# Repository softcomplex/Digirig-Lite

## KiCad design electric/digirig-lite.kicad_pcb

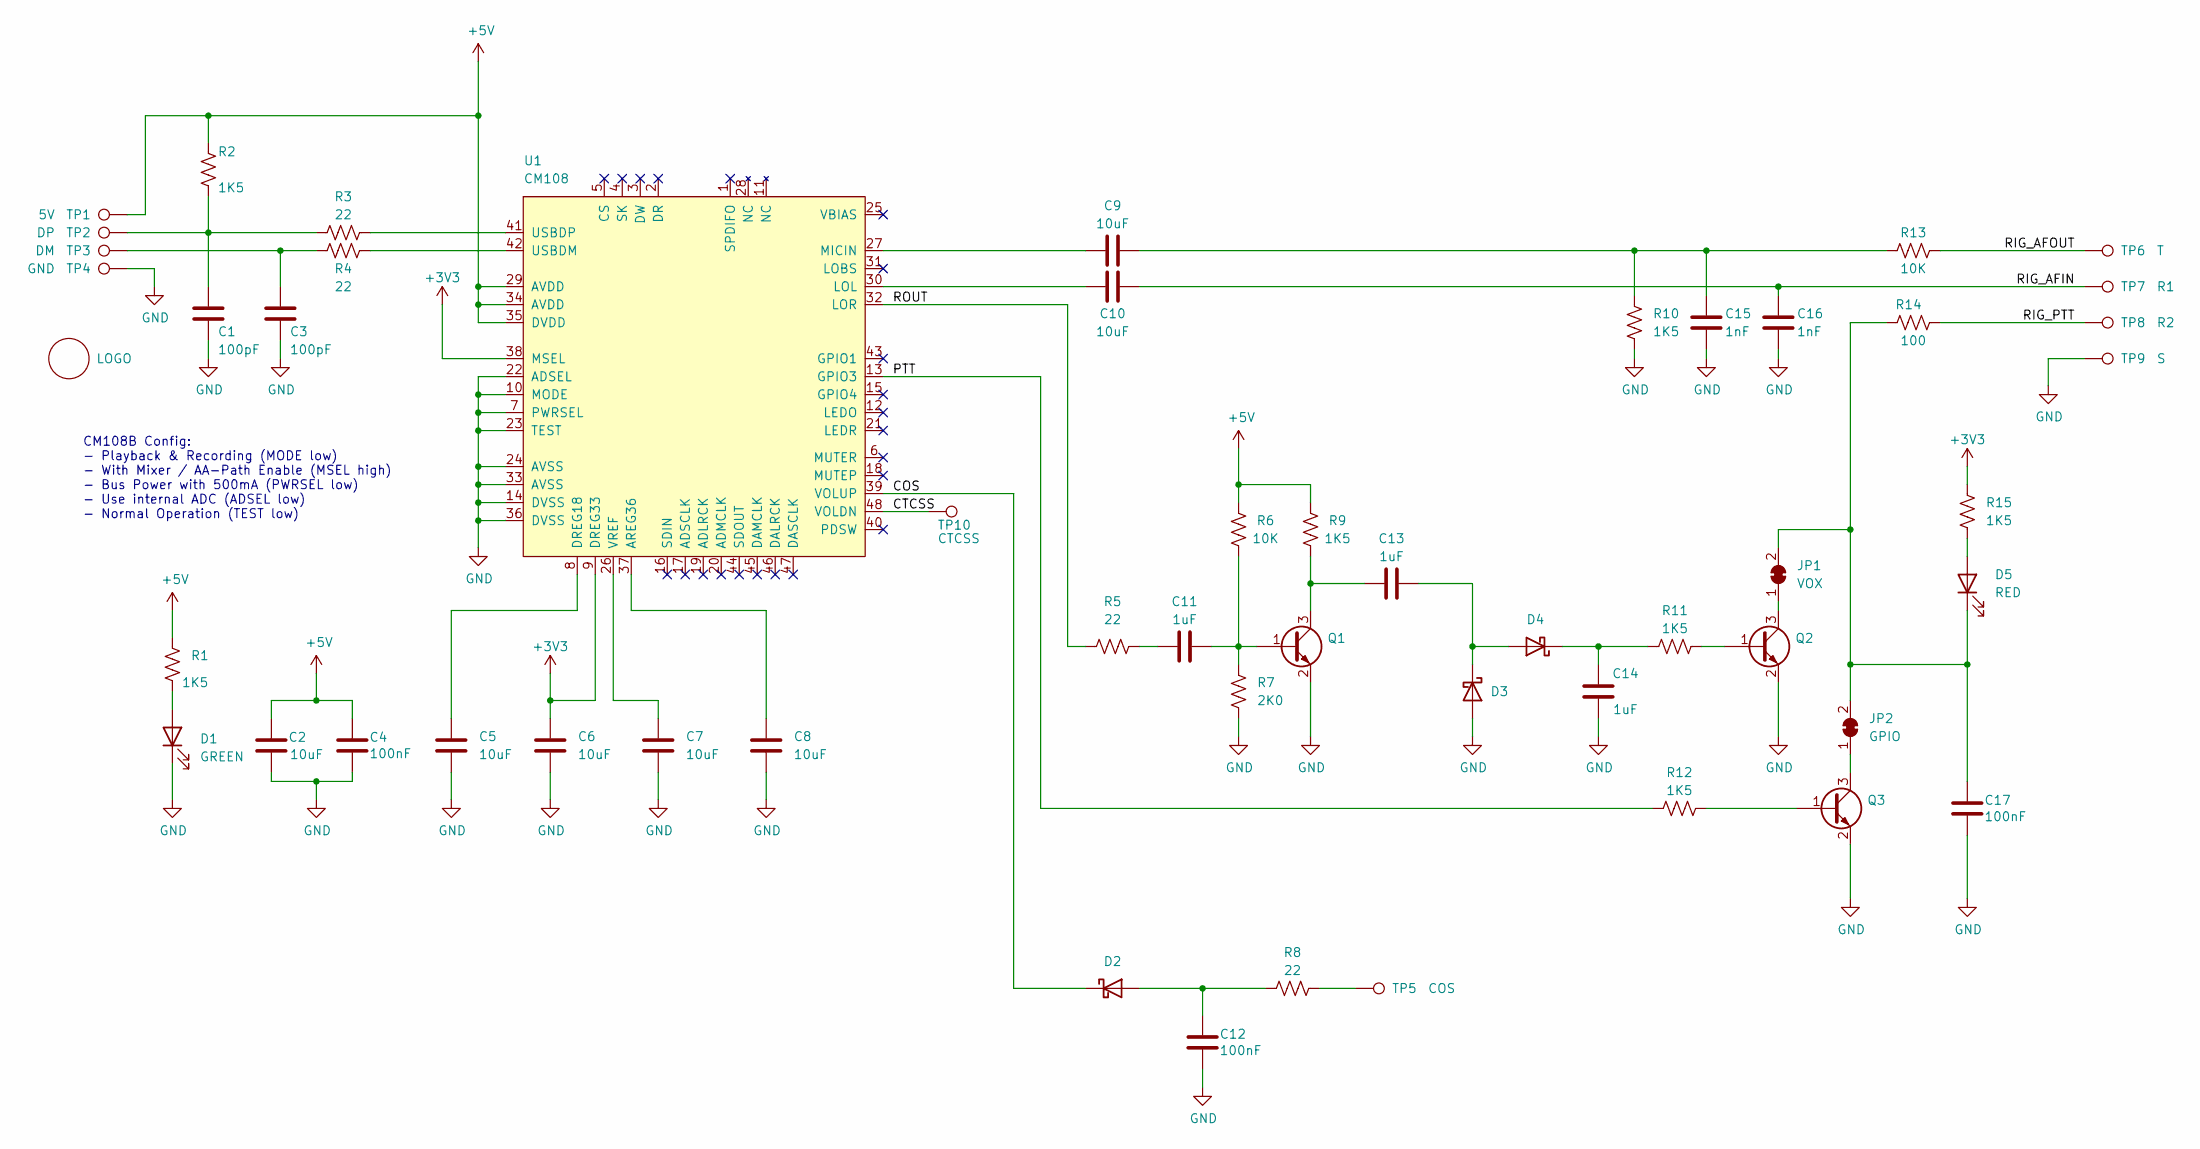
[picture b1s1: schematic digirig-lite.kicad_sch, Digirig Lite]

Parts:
C1, C3: 100pF; C_0402_1005Metric; LCSC C1546
C2, C5, C6, C7, C8, C9, C10: 10uF; C_0402_1005Metric; LCSC C15525
C4, C12, C17: 100nF; C_0402_1005Metric; LCSC C1525
C11, C13, C14: 1uF; C_0402_1005Metric; LCSC C52923
C15, C16: 1nF; C_0402_1005Metric; LCSC C1523
D1: GREEN; LED_0603_1608Metric; LCSC C3028829
D2, D3, D4: GS2005ELD; D_SOD-923; LCSC C18716421
D5: RED; LED_0603_1608Metric; LCSC C2286
JP1: VOX; SolderJumper-2_P1.3mm_Bridged_RoundedPad1.0x1.5mm
JP2: GPIO; SolderJumper-2_P1.3mm_Bridged_RoundedPad1.0x1.5mm
L1: LOGO; digirig-logo-6mm
Q1, Q2, Q3: MMBT5551L; SOT-23; LCSC C2145
R1, R2, R9, R10, R11, R12, R15: 1K5; R_0402_1005Metric; LCSC C25867
R3, R4, R5, R8: 22; R_0402_1005Metric; LCSC C25092
R6, R13: 10K; R_0402_1005Metric; LCSC C25744
R7: 2K0; R_0402_1005Metric; LCSC C4109
R14: 100; R_0402_1005Metric; LCSC C25076
TP1: 5V; TestPoint_Pad_D1.5mm
TP2: DP; TestPoint_Pad_D1.5mm
TP3: DM; TestPoint_Pad_D1.5mm
TP4: GND; TestPoint_Pad_D1.5mm
TP5: COS; TestPoint_Pad_D1.5mm
TP6: T; TestPoint_Pad_D1.5mm
TP7: R1; TestPoint_Pad_D1.5mm
TP8: R2; TestPoint_Pad_D1.5mm
TP9: S; TestPoint_Pad_D1.5mm
TP10: CTCSS; TestPoint_Pad_D1.5mm
U1: CM108; LQFP-48_7x7mm_P0.5mm; LCSC C371347

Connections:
+3V3: C6.1, R15.1, U1.9 (DREG33), U1.38 (MSEL)
+5V: C2.1, C4.1, R1.1, R2.2, R6.1, R9.1, TP1.1, U1.29 (AVDD), U1.34 (AVDD), U1.35 (DVDD)
/COS: D2.1 (K), U1.39 (VOLUP)
/CTCSS: TP10.1, U1.48 (VOLDN)
/PTT: R12.2, U1.13 (GPIO3)
/RIG_AFIN: C10.1, C16.1, TP7.1
/RIG_AFOUT: R13.1, TP6.1
/RIG_PTT: R14.1, TP8.1
/ROUT: R5.1, U1.32 (LOR)
GND: C1.2, C2.2, C3.2, C4.2, C5.2, C6.2, C7.2, C8.2, C12.2, C14.1, C15.2, C16.2, C17.2, D1.1 (K), D3.2 (A), Q1.2 (E), Q2.2 (E), Q3.2 (E), R7.2, R10.2, TP4.1, TP9.1, U1.7 (PWRSEL), U1.10 (MODE), U1.14 (DVSS), U1.22 (ADSEL), U1.23 (TEST), U1.24 (AVSS), U1.33 (AVSS), U1.36 (DVSS)
unnamed: C1.1, R2.1, R3.2, TP2.1
unnamed: C3.1, R4.2, TP3.1
unnamed: C11.2, R5.2
unnamed: C9.1, C15.1, R10.1, R13.2
unnamed: D1.2 (A), R1.2
unnamed: C12.1, D2.2 (A), R8.2
unnamed: C13.1, D3.1 (K), D4.2 (A)
unnamed: C14.2, D4.1 (K), R11.2
unnamed: D5.2 (A), R15.2
unnamed: C17.1, D5.1 (K), JP1.2 (B), JP2.2 (B), R14.2
unnamed: JP1.1 (A), Q2.3 (C)
unnamed: JP2.1 (A), Q3.3 (C)
unnamed: C11.1, Q1.1 (B), R6.2, R7.1
unnamed: C13.2, Q1.3 (C), R9.2
unnamed: Q2.1 (B), R11.1
unnamed: Q3.1 (B), R12.1
unnamed: R8.1, TP5.1
unnamed: C8.1, U1.37 (AREG36)
unnamed: C5.1, U1.8 (DREG18)
unnamed: C10.2, U1.30 (LOL)
unnamed: C9.2, U1.27 (MICIN)
unnamed: R4.1, U1.42 (USBDM)
unnamed: R3.1, U1.41 (USBDP)
unnamed: C7.1, U1.26 (VREF)

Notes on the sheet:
CM108B Config: - Playback & Recording (MODE low) - With Mixer / AA-Path Enable (MSEL high) - Bus Power with 500mA (PWRSEL low) - Use internal ADC (ADSEL low) - Normal Operation (TEST low)

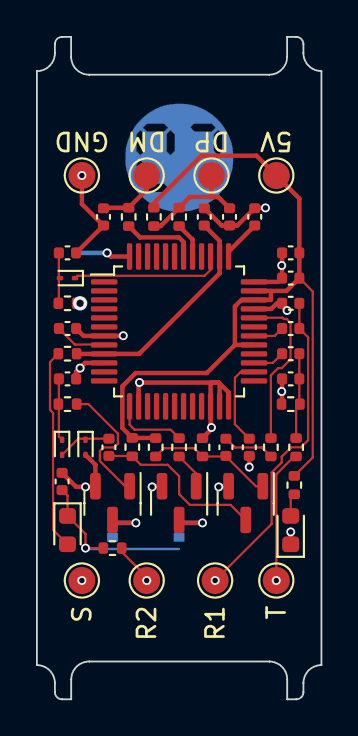
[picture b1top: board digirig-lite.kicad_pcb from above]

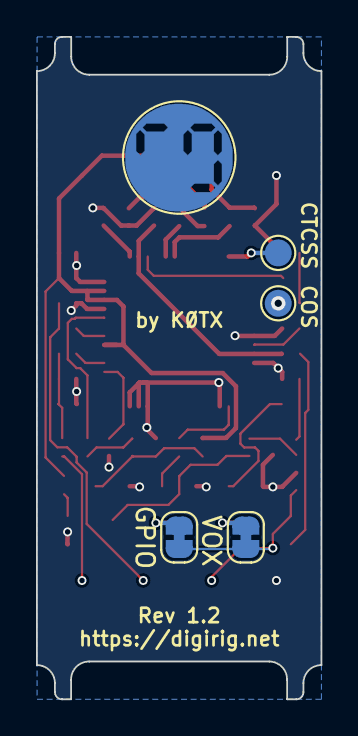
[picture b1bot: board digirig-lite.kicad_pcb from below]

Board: 2 copper layers, 15.8 x 36.8 mm, 54 parts (4 on the bottom side), 34 nets.

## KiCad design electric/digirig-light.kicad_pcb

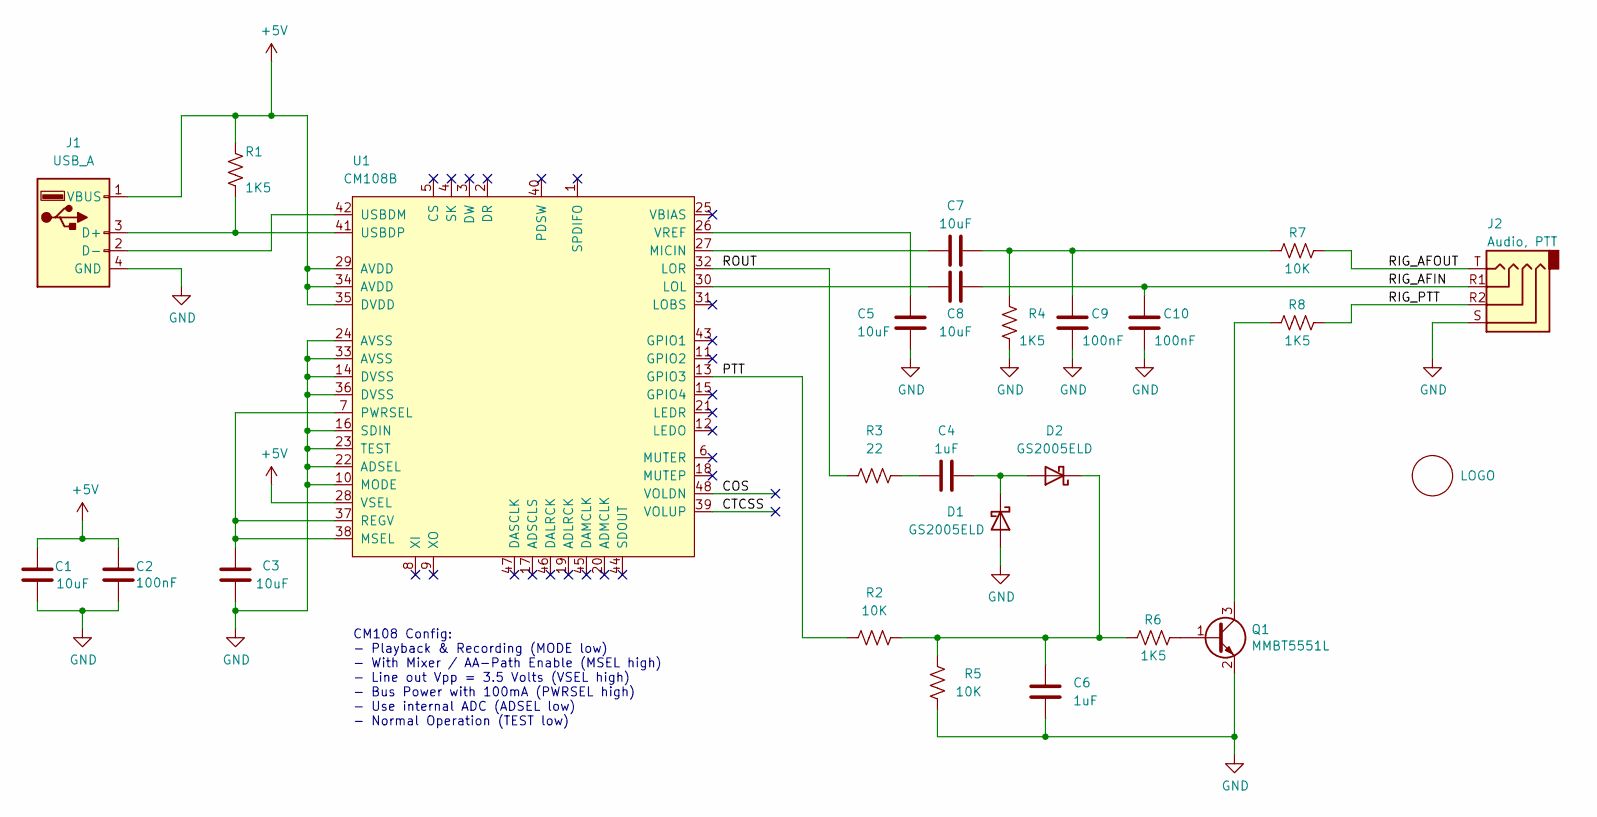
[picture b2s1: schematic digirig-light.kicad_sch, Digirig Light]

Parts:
C1, C3, C5, C7, C8: 10uF; C_0402_1005Metric; LCSC C15525
C2, C9, C10: 100nF; C_0402_1005Metric; LCSC C1525
C4, C6: 1uF; C_0402_1005Metric; LCSC C52923
D1, D2: GS2005ELD; D_SOD-923; LCSC C18716421
J1: USB_A; USB_A_PCB_traces_small
J2: PJ-320A; Jack_3.5mm_PJ320D_Horizontal; LCSC C431535
L1: LOGO; digirig-logo-6mm
Q1: MMBT5551L; SOT-23; LCSC C152516
R1, R4, R6, R8: 1K5; R_0402_1005Metric; LCSC C25867
R2, R5, R7: 10K; R_0402_1005Metric; LCSC C25744
R3: 22; R_0402_1005Metric; MPN C25092
U1: CM108B; LQFP-48_7x7mm_P0.5mm; LCSC C371347

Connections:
+5V: C1.1, C2.1, J1.1 (VBUS), R1.2, U1.28 (VSEL), U1.29 (AVDD), U1.34 (AVDD), U1.35 (DVDD)
/COS: U1.48 (VOLDN)
/CTCSS: U1.39 (VOLUP)
/PTT: R2.2, U1.13 (GPIO3)
/RIG_AFIN: C8.1, C10.1, J2.R1
/RIG_AFOUT: J2.T, R7.1
/RIG_PTT: J2.R2, R8.1
/ROUT: R3.1, U1.32 (LOR)
GND: C1.2, C2.2, C3.1, C5.2, C6.2, C9.2, C10.2, D1.2 (A), J1.4 (GND), J2.S, Q1.2 (E), R4.2, R5.1, U1.10 (MODE), U1.14 (DVSS), U1.16 (SDIN), U1.22 (ADSEL), U1.23 (TEST), U1.24 (AVSS), U1.33 (AVSS), U1.36 (DVSS)
unnamed: C4.2, R3.2
unnamed: C7.1, C9.1, R4.1, R7.2
unnamed: C4.1, D1.1 (K), D2.2 (A)
unnamed: C6.1, D2.1 (K), R2.1, R5.2, R6.2
unnamed: J1.3 (D+), R1.1, U1.41 (USBDP)
unnamed: J1.2 (D-), U1.42 (USBDM)
unnamed: Q1.1 (B), R6.1
unnamed: Q1.3 (C), R8.2
unnamed: C8.2, U1.30 (LOL)
unnamed: C7.2, U1.27 (MICIN)
unnamed: C3.2, U1.7 (PWRSEL), U1.37 (REGV), U1.38 (MSEL)
unnamed: C5.1, U1.26 (VREF)

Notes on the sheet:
CM108 Config: - Playback & Recording (MODE low) - With Mixer / AA-Path Enable (MSEL high) - Line out Vpp = 3.5 Volts (VSEL high) - Bus Power with 100mA (PWRSEL high) - Use internal ADC (ADSEL low) - Normal Operation (TEST low)

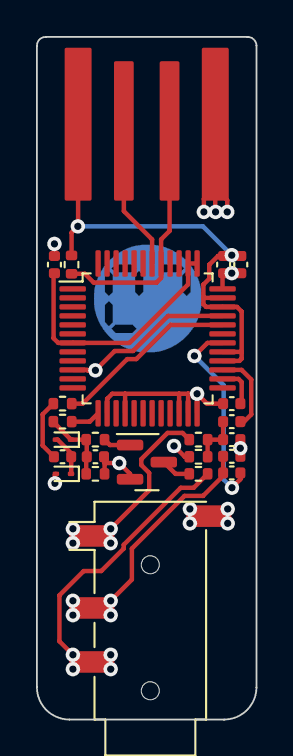
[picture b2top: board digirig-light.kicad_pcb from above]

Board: 2 copper layers, 12.2 x 37.9 mm, 25 parts (0 on the bottom side), 19 nets.

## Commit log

2024-03-08 Revision 1.1
    - PTT by tone circuit modification
    - CM108B output voltage config change from 2.5V to 3.5V
2024-04-04 Revision 1.2
    - added amplification for VOX PTT on right audio channel
    - added LED indication for power and PTT
    - PCB redone for cable form factor
    - project renamed from Digirig Light to Digirig Lite
2025-08-05 Revision 1.2

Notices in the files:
electric/digirig-light.kicad_sch:
GNU General Public License v3.0
